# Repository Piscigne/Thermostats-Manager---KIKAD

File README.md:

# Thermostats-Manager---KIKAD

Parts of project
================
Main page 
https://github.com/Piscigne/Thermostats-Manager

Target
======
Designed for managing 6 thermostats in the home.
Full MQTT exchanges with the Jeedoom domotic environment

Schema
------

PCB
---

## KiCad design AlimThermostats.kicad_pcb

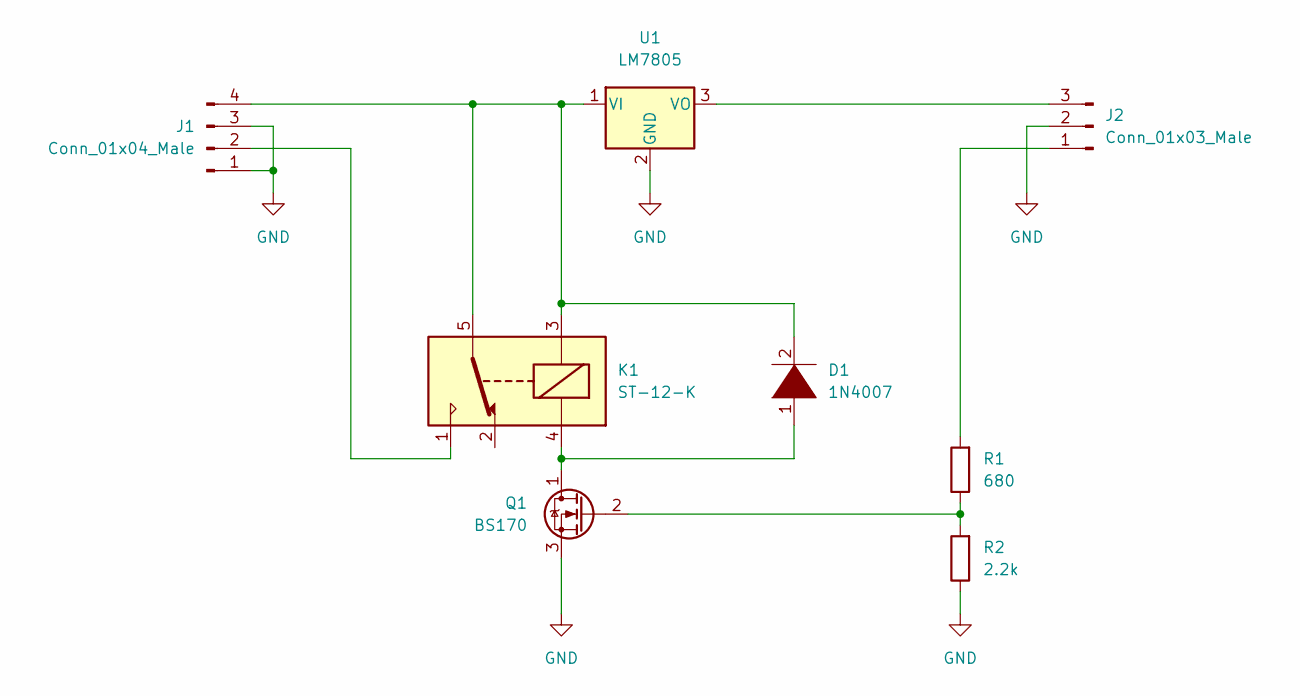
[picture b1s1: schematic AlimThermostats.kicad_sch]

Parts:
D1: 1N4007; D_DO-41_SOD81_P10.16mm_Horizontal
J1: Conn_01x04_Male; PhoenixContact_MCV_1,5_4-G-3.5_1x04_P3.50mm_Vertical
J2: Conn_01x03_Male; PhoenixContact_MCV_1,5_3-G-3.5_1x03_P3.50mm_Vertical
K1: ST-12-K; Relay_SPDT_HsinDa_Y14
Q1: BS170; TO-92_Inline
R1: 680; R_Axial_DIN0204_L3.6mm_D1.6mm_P7.62mm_Horizontal
R2: 2.2k; R_Axial_DIN0204_L3.6mm_D1.6mm_P7.62mm_Horizontal
U1: LM7805; TO-220-3_Vertical

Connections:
GND: J1.1, J1.3, J2.2, Q1.3 (S), R2.1, U1.2 (GND)
unnamed: D1.1 (K), K1.4, Q1.1 (D)
unnamed: D1.2 (A), J1.4, K1.3, K1.5, K1.6, U1.1 (VI)
unnamed: J2.1, R1.2
unnamed: J2.3, U1.3 (VO)
unnamed: J1.2, K1.1
unnamed: Q1.2 (G), R1.1, R2.2

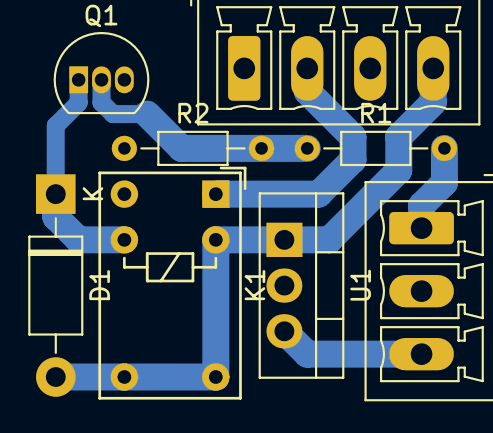
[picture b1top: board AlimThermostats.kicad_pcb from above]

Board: 2 copper layers, 8 parts (0 on the bottom side), 7 nets.
